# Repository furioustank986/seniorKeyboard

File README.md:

# seniorKeyboard
This is a keyboard project aimed at Korean seniors to make the action of inputing Korean Characters into a computer easier.

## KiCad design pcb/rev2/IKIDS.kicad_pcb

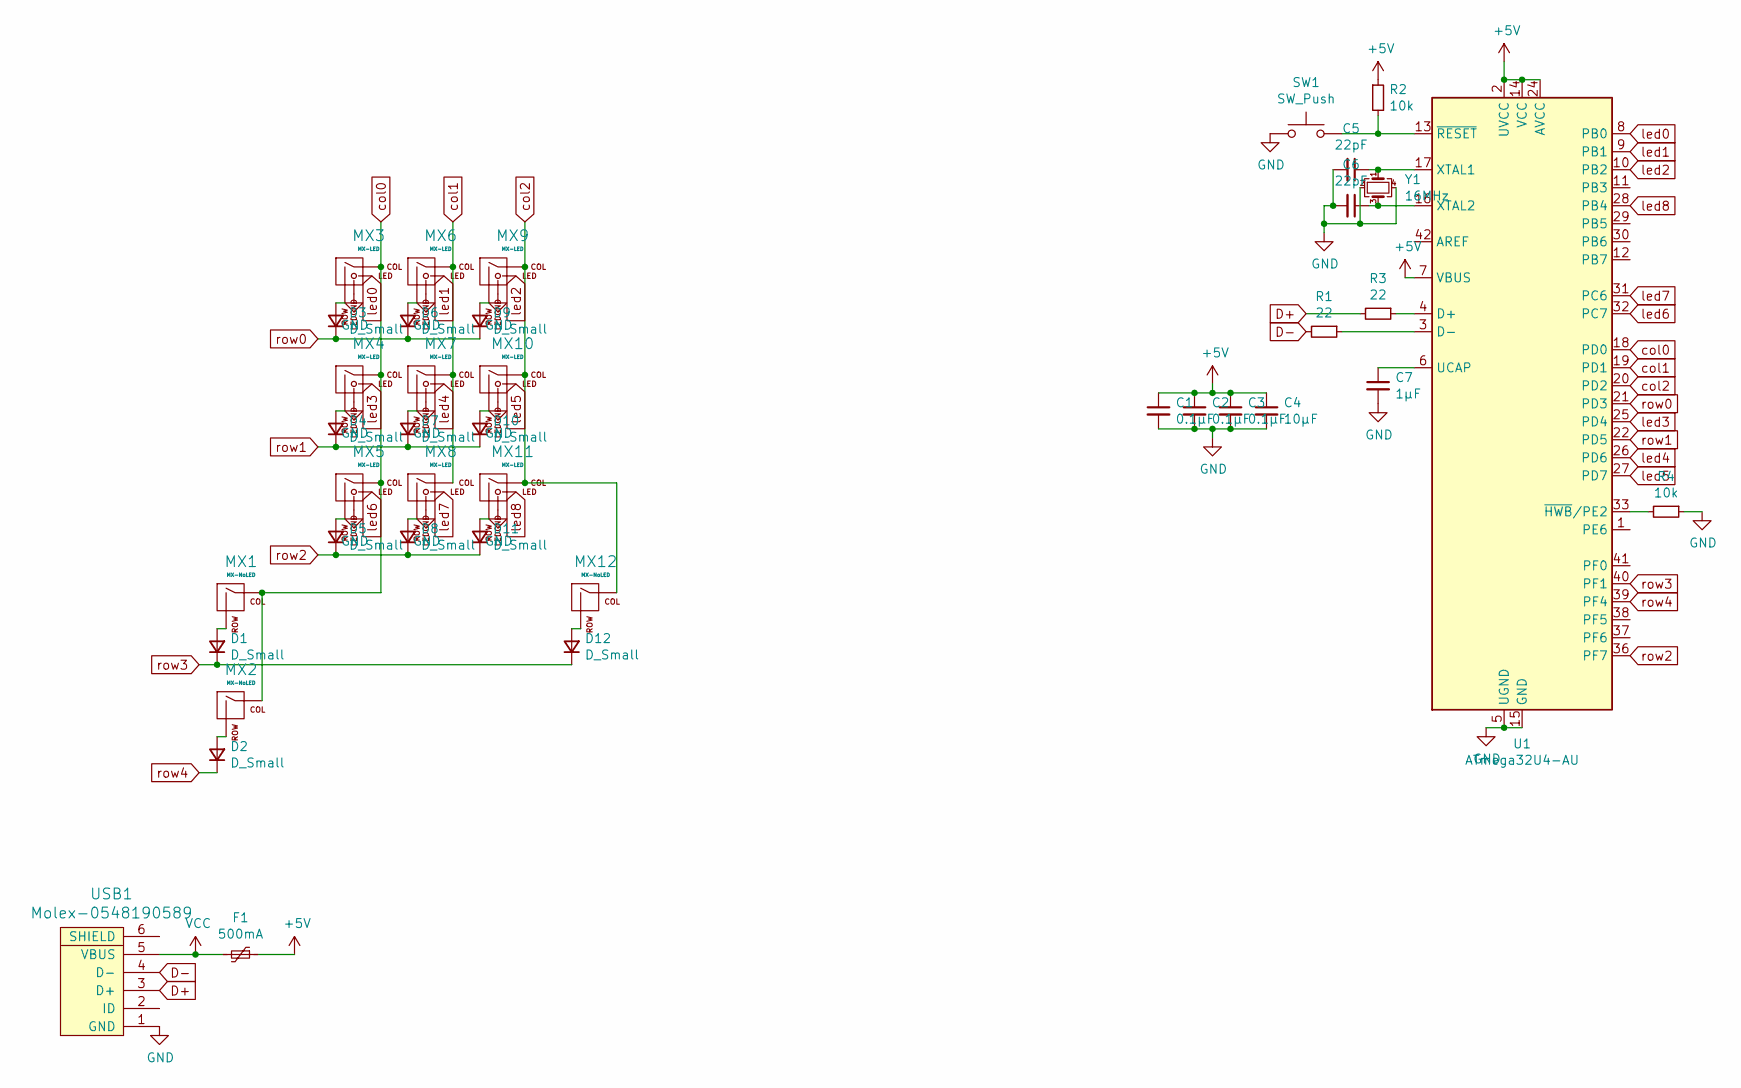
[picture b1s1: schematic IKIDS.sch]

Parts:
C1, C2, C3: 0.1µF; C_0805_2012Metric
C4: 10µF; C_0805_2012Metric
C5, C6: 22pF; C_0805_2012Metric
C7: 1µF; C_0805_2012Metric
D1, D2, D3, D4, D5, D6, D7, D8, D9, D10, D11, D12: D_Small; D_SOD-123
F1: 500mA; Fuse_1206_3216Metric
MX1, MX2, MX12: MX-NoLED; MX-1.5U-NoLED
MX3, MX4, MX5, MX6, MX7, MX8, MX9, MX10, MX11: MX-LED; MX-1U
R1, R3: 22; R_0805_2012Metric
R2, R4: 10k; R_0805_2012Metric
SW1: SW_Push; SKQG-1155865
U1: ATmega32U4-AU; TQFP-44_10x10mm_P0.8mm
USB1: Molex-0548190589
Y1: 16MHz; Crystal_SMD_3225-4Pin_3.2x2.5mm

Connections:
+5V: C1.1, C2.1, C3.1, C4.1, F1.1, R2.1, U1.2 (UVCC), U1.7 (VBUS), U1.14 (VCC), U1.24 (AVCC), U1.34 (VCC), U1.44 (AVCC)
D+: R3.2, USB1.3 (D+)
D-: R1.2, USB1.4 (D-)
GND: C1.2, C2.2, C3.2, C4.2, C5.2, C6.2, C7.2, MX3.4 (LEDGND), MX4.4 (LEDGND), MX5.4 (LEDGND), MX6.4 (LEDGND), MX7.4 (LEDGND), MX8.4 (LEDGND), MX9.4 (LEDGND), MX10.4 (LEDGND), MX11.4 (LEDGND), R4.1, SW1.1, U1.5 (UGND), U1.15 (GND), U1.23 (GND), U1.35 (GND), U1.43 (GND), USB1.1 (GND), Y1.2, Y1.4
unnamed: C5.1, U1.17 (XTAL1), Y1.1
unnamed: C6.1, U1.16 (XTAL2), Y1.3
unnamed: C7.1, U1.6 (UCAP)
unnamed: D1.2 (A), MX1.2 (ROW)
unnamed: D2.2 (A), MX2.2 (ROW)
unnamed: D3.2 (A), MX3.2 (ROW)
unnamed: D4.2 (A), MX4.2 (ROW)
unnamed: D5.2 (A), MX5.2 (ROW)
unnamed: D6.2 (A), MX6.2 (ROW)
unnamed: D7.2 (A), MX7.2 (ROW)
unnamed: D8.2 (A), MX8.2 (ROW)
unnamed: D9.2 (A), MX9.2 (ROW)
unnamed: D10.2 (A), MX10.2 (ROW)
unnamed: D11.2 (A), MX11.2 (ROW)
unnamed: D12.2 (A), MX12.2 (ROW)
unnamed: R1.1, U1.3 (D-)
unnamed: R2.2, SW1.2, U1.13 (~RESET)
unnamed: R3.1, U1.4 (D+)
unnamed: R4.2, U1.33 (~HWB~/PE2)
VCC: F1.2, USB1.5 (VBUS)
col0: MX1.1 (COL), MX2.1 (COL), MX3.1 (COL), MX4.1 (COL), MX5.1 (COL), U1.18 (PD0)
col1: MX6.1 (COL), MX7.1 (COL), MX8.1 (COL), U1.19 (PD1)
col2: MX9.1 (COL), MX10.1 (COL), MX11.1 (COL), MX12.1 (COL), U1.20 (PD2)
led0: MX3.3 (LED), U1.8 (PB0)
led1: MX6.3 (LED), U1.9 (PB1)
led2: MX9.3 (LED), U1.10 (PB2)
led3: MX4.3 (LED), U1.25 (PD4)
led4: MX7.3 (LED), U1.26 (PD6)
led5: MX10.3 (LED), U1.27 (PD7)
led6: MX5.3 (LED), U1.32 (PC7)
led7: MX8.3 (LED), U1.31 (PC6)
led8: MX11.3 (LED), U1.28 (PB4)
row0: D3.1 (K), D6.1 (K), D9.1 (K), U1.21 (PD3)
row1: D4.1 (K), D7.1 (K), D10.1 (K), U1.22 (PD5)
row2: D5.1 (K), D8.1 (K), D11.1 (K), U1.36 (PF7)
row3: D1.1 (K), D12.1 (K), U1.40 (PF1)
row4: D2.1 (K), U1.39 (PF4)

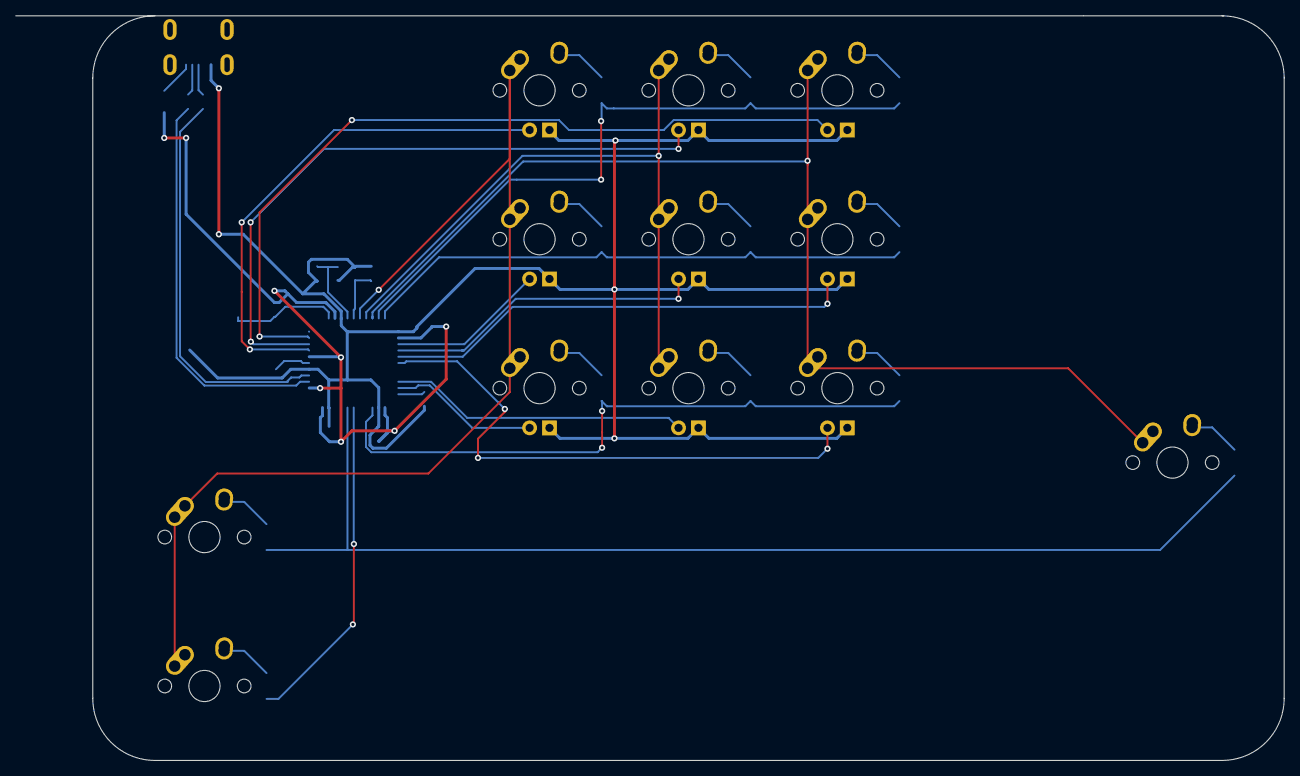
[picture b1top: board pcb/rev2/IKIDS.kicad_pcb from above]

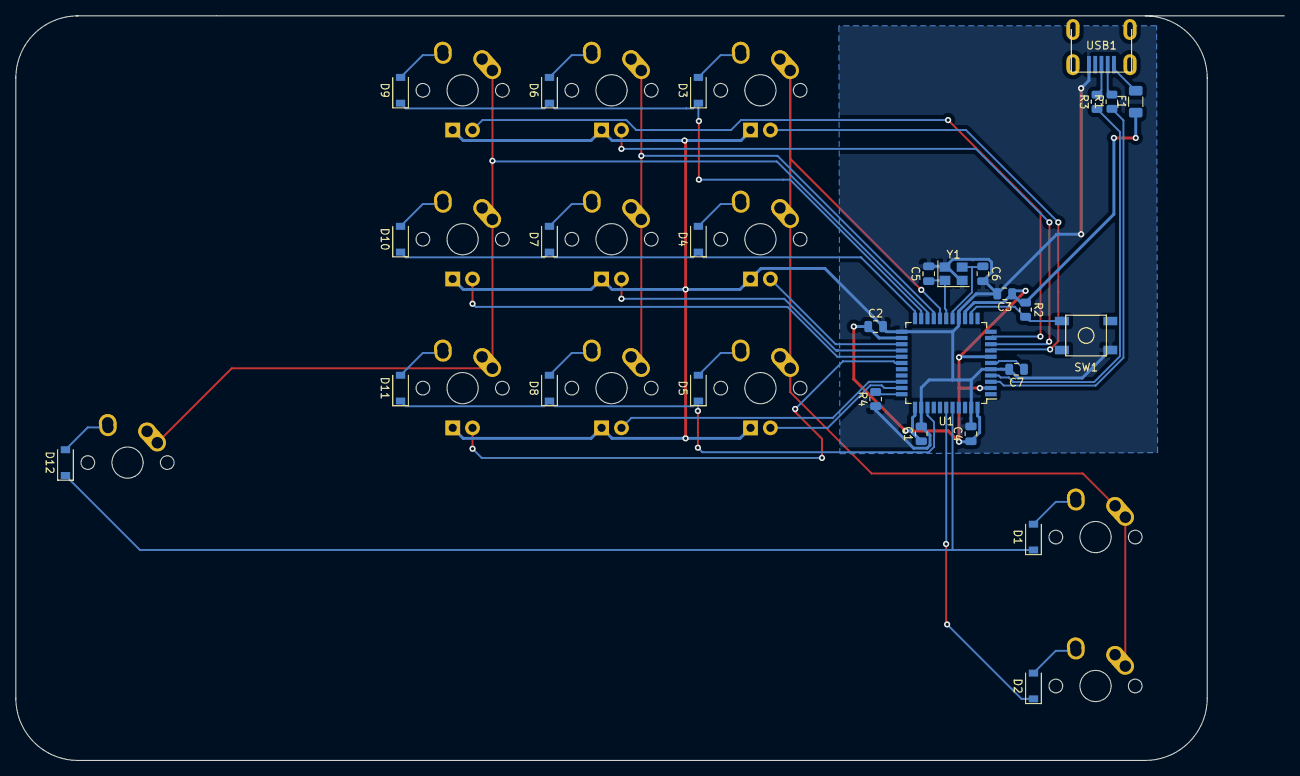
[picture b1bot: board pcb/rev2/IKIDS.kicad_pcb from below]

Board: 2 copper layers, 162.2 x 95.2 mm, 40 parts (28 on the bottom side), 41 nets.

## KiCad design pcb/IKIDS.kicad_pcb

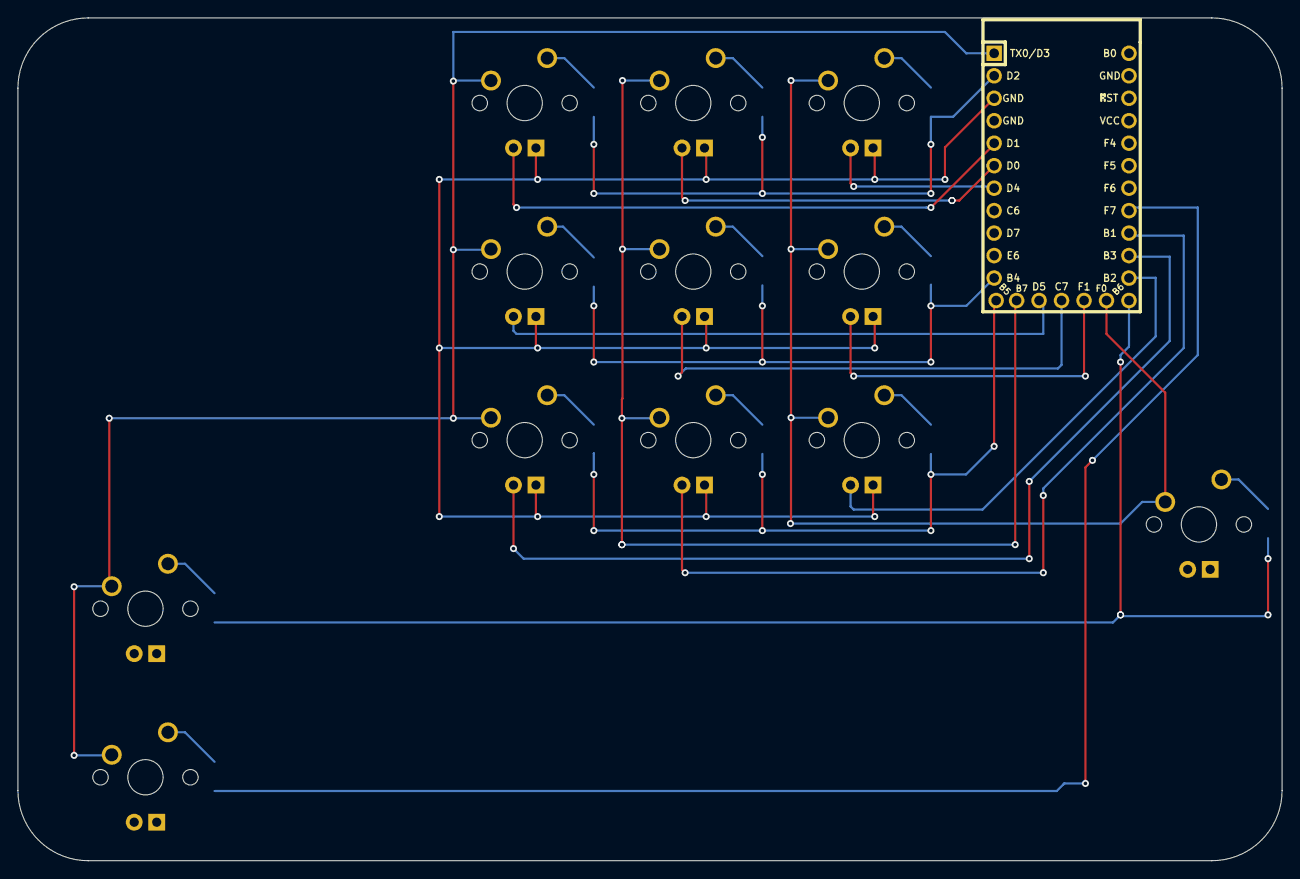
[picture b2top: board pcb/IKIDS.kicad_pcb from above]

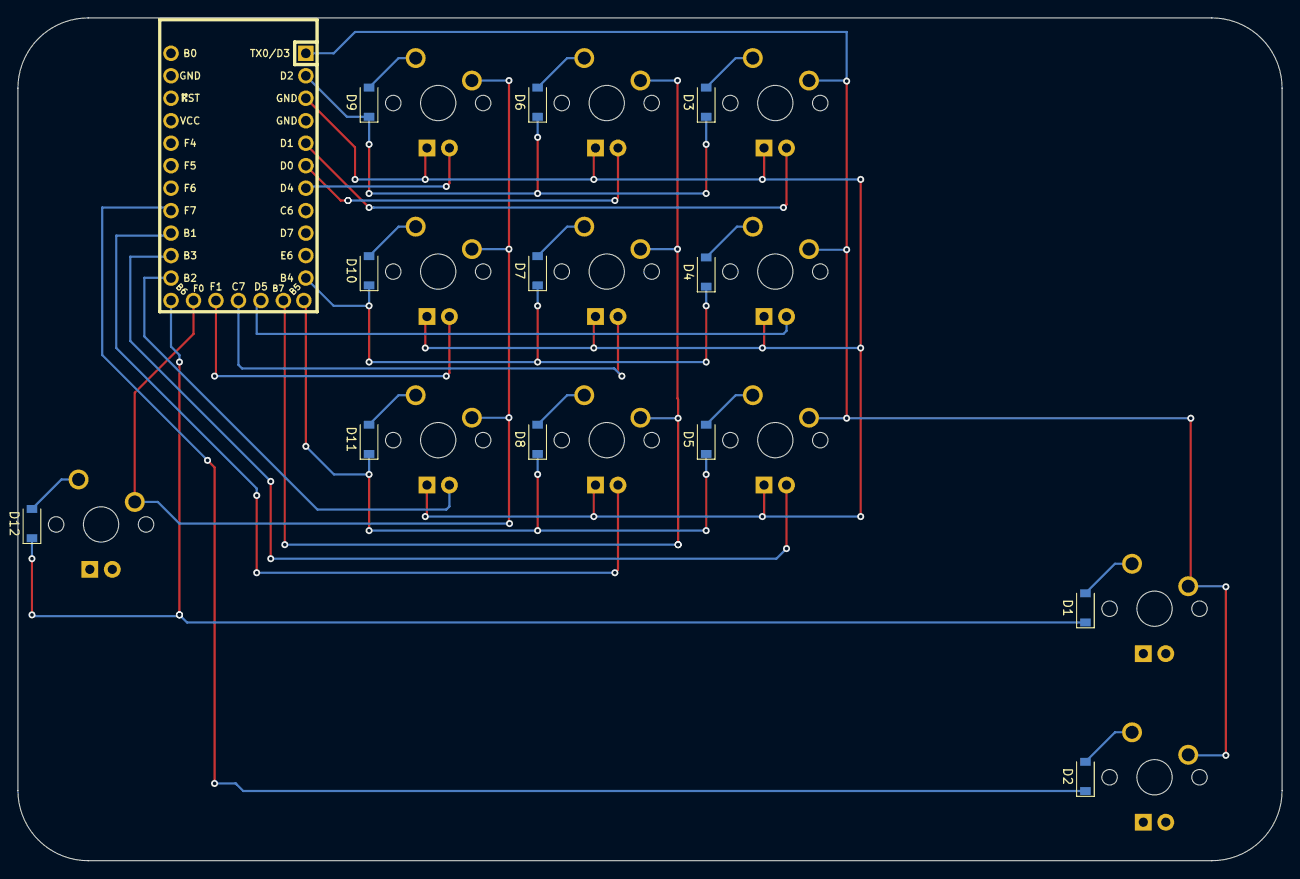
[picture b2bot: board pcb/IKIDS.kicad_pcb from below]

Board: 2 copper layers, 142.9 x 95.3 mm, 25 parts (12 on the bottom side), 30 nets.

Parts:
D1, D2, D3, D4, D5, D6, D7, D8, D9, D10, D11, D12: D_Small; D_SOD-123
MX1, MX2: MX-LED; MXOnly-1.5U
MX3, MX4, MX5, MX6, MX7, MX8, MX9, MX10, MX11, MX12: MX-LED; MXOnly-1U
U1: Elite-C

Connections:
unnamed: D1.2, MX1.2
unnamed: D2.2, MX2.2
unnamed: D3.2, MX3.2
unnamed: D4.2, MX4.2
unnamed: D5.2, MX5.2
unnamed: D6.2, MX6.2
unnamed: D7.2, MX7.2
unnamed: D8.2, MX8.2
unnamed: D9.2, MX9.2
unnamed: D10.2, MX10.2
unnamed: D11.2, MX11.2
unnamed: D12.2, MX12.2
col1: MX1.1, MX2.1, MX3.1, MX4.1, MX5.1, U1.1
col2: MX6.1, MX7.1, MX8.1, U1.25
col3: MX9.1, MX10.1, MX11.1, MX12.1, U1.29
gnd: MX3.4, MX4.4, MX5.4, MX6.4, MX7.4, MX8.4, MX9.4, MX10.4, MX11.4, U1.3
led1: MX3.3, U1.5
led2: MX6.3, U1.6
led3: MX9.3, U1.7
led4: MX4.3, U1.26
led5: MX7.3, U1.27
led6: MX10.3, U1.28
led7: MX5.3, U1.15
led8: MX8.3, U1.16
led9: MX11.3, U1.14
row1: D3.1, D6.1, D9.1, U1.2
row2: D4.1, D7.1, D10.1, U1.11
row3: D5.1, D8.1, D11.1, U1.12
row4: D1.1, D12.1, U1.13
row5: D2.1, U1.17

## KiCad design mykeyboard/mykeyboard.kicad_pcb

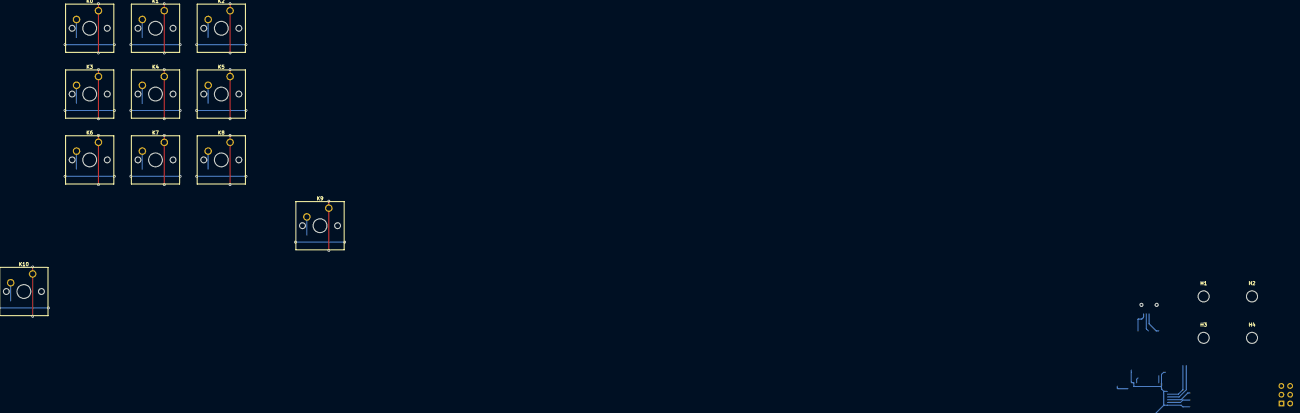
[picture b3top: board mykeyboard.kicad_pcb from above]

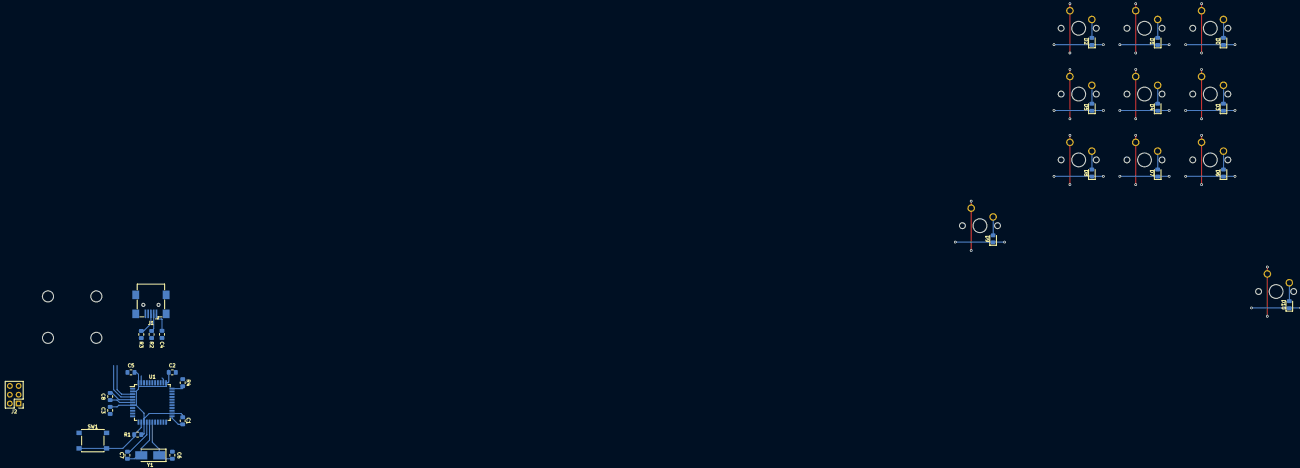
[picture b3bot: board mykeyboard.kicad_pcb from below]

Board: 2 copper layers, 43 parts (28 on the bottom side), 30 nets.

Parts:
C1, C2, C3, C4: 0.1u; C_0805_2012Metric_Pad1.15x1.40mm_HandSolder
C5: 4.7u; C_0805_2012Metric_Pad1.15x1.40mm_HandSolder
C6, C7: 22p; C_0805_2012Metric_Pad1.15x1.40mm_HandSolder
C8: 1u; C_0805_2012Metric_Pad1.15x1.40mm_HandSolder
D0, D1, D2, D3, D4, D5, D6, D7, D8, D9, D10: D; D_0805_2012Metric_Pad1.15x1.40mm_HandSolder
H1, H2, H3, H4: MountingHole; MountingHole_3.2mm_M3_DIN965
J1: USB_mini_micro_B; USB_Mini-B_Wuerth_65100516121_Horizontal
J2: Conn_02x03_Odd_Even; PinHeader_2x03_P2.54mm_Vertical
K0, K1, K2, K3, K4, K5, K6, K7, K8, K9: KEYSW; SW_Cherry_MX_1.00u_PCB
K10: KEYSW; SW_Cherry_MX_2.00u_PCB
R1, R4: 10k; R_0805_2012Metric_Pad1.15x1.40mm_HandSolder
R2, R3: 22R; R_0805_2012Metric_Pad1.15x1.40mm_HandSolder
SW1: SW_Push; SW_Push_1P1T_NO_6x6mm_H9.5mm
U1: ATmega32U4-AU; TQFP-44_10x10mm_P0.8mm
Y1: Crystal; Crystal_SMD_5032-2Pin_5.0x3.2mm_HandSoldering

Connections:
/Col_0: K0.1, K3.1, K6.1, K9.1, K10.1, U1.32
/Col_1: K1.1, K4.1, K7.1, U1.31
/Col_2: K2.1, K5.1, K8.1, U1.30
/Row_0: D0.1, D1.1, D2.1, U1.18
/Row_1: D3.1, D4.1, D5.1, U1.12
/Row_2: D6.1, D7.1, D8.1, J2.2, U1.11
/Row_3: D9.1, J2.4, U1.10
/Row_4: D10.1, J2.3, U1.9
GND: C1.2, C2.2, C3.2, C4.2, C5.2, C6.2, C7.2, C8.2, J1.5, J1.6, J2.5, R4.1, SW1.1, U1.5, U1.15, U1.23, U1.35, U1.43
unnamed: C6.1, U1.17, Y1.1
unnamed: C7.1, U1.16, Y1.2
unnamed: C8.1, U1.6
unnamed: D0.2, K0.2
unnamed: D1.2, K1.2
unnamed: D2.2, K2.2
unnamed: D3.2, K3.2
unnamed: D4.2, K4.2
unnamed: D5.2, K5.2
unnamed: D6.2, K6.2
unnamed: D7.2, K7.2
unnamed: D8.2, K8.2
unnamed: D9.2, K9.2
unnamed: D10.2, K10.2
unnamed: J1.2, R2.2
unnamed: J1.3, R3.2
unnamed: R1.1, SW1.2, U1.13
unnamed: R2.1, U1.4
unnamed: R3.1, U1.3
unnamed: R4.2, U1.33
VCC: C1.1, C2.1, C3.1, C4.1, C5.1, J1.1, J2.1, R1.2, U1.2, U1.7, U1.14, U1.24, U1.34, U1.44

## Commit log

2021-04-11 Added keyboard layout as well as pcb files
2021-04-11 Changed name of layout json
2021-04-11 Added pcb file
2021-04-11 KiCad footprints by ai03 added
2021-04-11 removed footprints
2021-04-11 Footprints added
2021-04-11 Added footprints to project
2021-04-11 added proton c footprint
2021-04-11 added proton c footprint to project
2021-04-12 updated layout.json
2021-04-12 added korean support for IKIDS firmware
2021-04-12 added shift support
2021-04-12 removed obsolete pcb file
2021-04-12 added actual pcb files
2021-04-12 updated firmware
2021-04-12 firmware updated to fit elite-c
2021-04-12 added macro function
2021-04-12 added pcb schematics
2021-04-12 updated firmware and pcb schematics
2021-04-12 Created PCB with Elite-C usage in mind. The hardware now supports led.
2021-04-13 Updated PCB routing to be thicker and more organized. Increased distance from pad to trace. TODO: connect grid to MCU
2021-04-13 Hooked up main matrix and ground pins for the LED to the MCU.
2021-04-13 Hooked up top 3 LEDs
2021-04-13 hooked up bottom 3 LEDS
2021-04-13 Finished PCB and updated Schematics to fit PCB
2021-04-13 updated diode footprint to D_SOD-123
2021-04-13 Added 3D PCB files for case modeling
2021-04-13 Flipped Elite-c for easier case making.
2021-04-13 added gerber files for manufacturing
2021-04-14 added case files
2021-04-14 Removed unnecessary files
2021-04-14 Updated files
2021-04-14 re-organized PCB files
2021-04-15 added rev2 PCB schematics that do not require an elite-c. Currently on USB Mini, to be updated to use usb-c.
2021-04-15 brought over part library from ai03's Voyager60 for USB C support
2021-04-15 Added finished PCB to repo
2021-04-16 added PCB files that doesn't require elite-c
2021-04-17 Added logo to PCB
